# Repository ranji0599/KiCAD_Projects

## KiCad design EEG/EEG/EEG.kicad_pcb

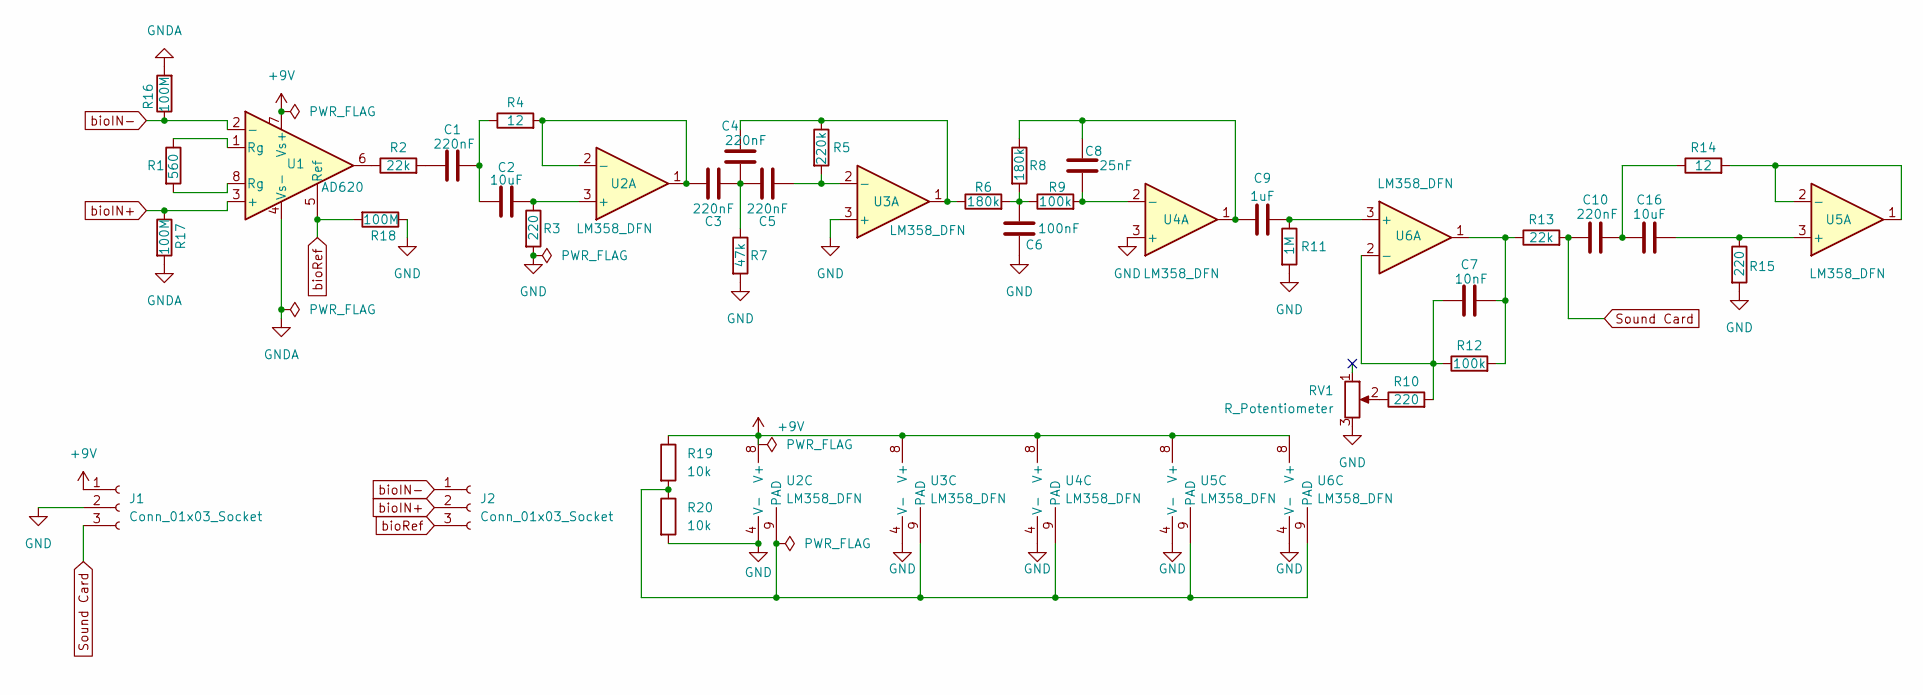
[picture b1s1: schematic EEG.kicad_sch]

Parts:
C1, C3, C4, C5, C10: 220nF; C_0805_2012Metric
C2, C16: 10uF; C_0805_2012Metric
C6: 100nF; C_0805_2012Metric
C7: 10nF; C_0805_2012Metric
C8: 25nF; C_0805_2012Metric
C9: 1uF; C_0805_2012Metric
J1, J2: Conn_01x03_Socket; JST_EH_S3B-EH_1x03_P2.50mm_Horizontal
R1: 560; R_0805_2012Metric
R2, R13: 22k; R_0805_2012Metric
R3, R10, R15: 220; R_0805_2012Metric
R4, R14: 12; R_0805_2012Metric
R5: 220k; R_0805_2012Metric
R6, R8: 180k; R_0805_2012Metric
R7: 47k; R_0805_2012Metric
R9, R12: 100k; R_0805_2012Metric
R11: 1M; R_0805_2012Metric
R16, R17, R18: 100M; R_0805_2012Metric
R19, R20: 10k; R_0805_2012Metric
RV1: R_Potentiometer; Potentiometer_ACP_CA6-H2,5_Horizontal
U1: AD620; SOIC-8_5.3x6.2mm_P1.27mm
U2, U3, U4, U5, U6: LM358_DFN; DFN-8-1EP_2x2mm_P0.5mm_EP1.05x1.75mm

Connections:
+9V: J1.1, R19.1, U1.7 (Vs+), U2.8 (V+), U3.8 (V+), U4.8 (V+), U5.8 (V+), U6.8 (V+)
unnamed: C1.1, R2.2
unnamed: C1.2, C2.1, R4.1
unnamed: C3.2, C4.2, C5.1, R7.1
unnamed: C4.1, R5.1, R6.1, U3.1
unnamed: C6.1, R6.2, R8.2, R9.1
unnamed: C7.2, R12.2, R13.1, U6.1
unnamed: C8.1, C9.1, R8.1, U4.1
unnamed: C10.2, C16.1, R14.1
unnamed: R1.1, U1.1 (Rg)
unnamed: R1.2, U1.8 (Rg)
unnamed: R2.1, U1.6
unnamed: R10.1, RV1.2
unnamed: C2.2, R3.1, U2.3 (+)
unnamed: C3.1, R4.2, U2.1, U2.2 (-)
unnamed: R19.2, R20.1, U2.9 (PAD), U3.9 (PAD), U4.9 (PAD), U5.9 (PAD), U6.9 (PAD)
unnamed: C5.2, R5.2, U3.2 (-)
unnamed: C8.2, R9.2, U4.2 (-)
unnamed: C16.2, R15.1, U5.3 (+)
unnamed: R14.2, U5.1, U5.2 (-)
unnamed: C9.2, R11.1, U6.3 (+)
unnamed: C7.1, R10.2, R12.1, U6.2 (-)
Sound Card: C10.1, J1.3, R13.2
bioIN+: J2.2, R17.1, U1.3 (+)
bioIN-: J2.1, R16.1, U1.2 (-)
bioRef: J2.3, R18.2, U1.5 (Ref)

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
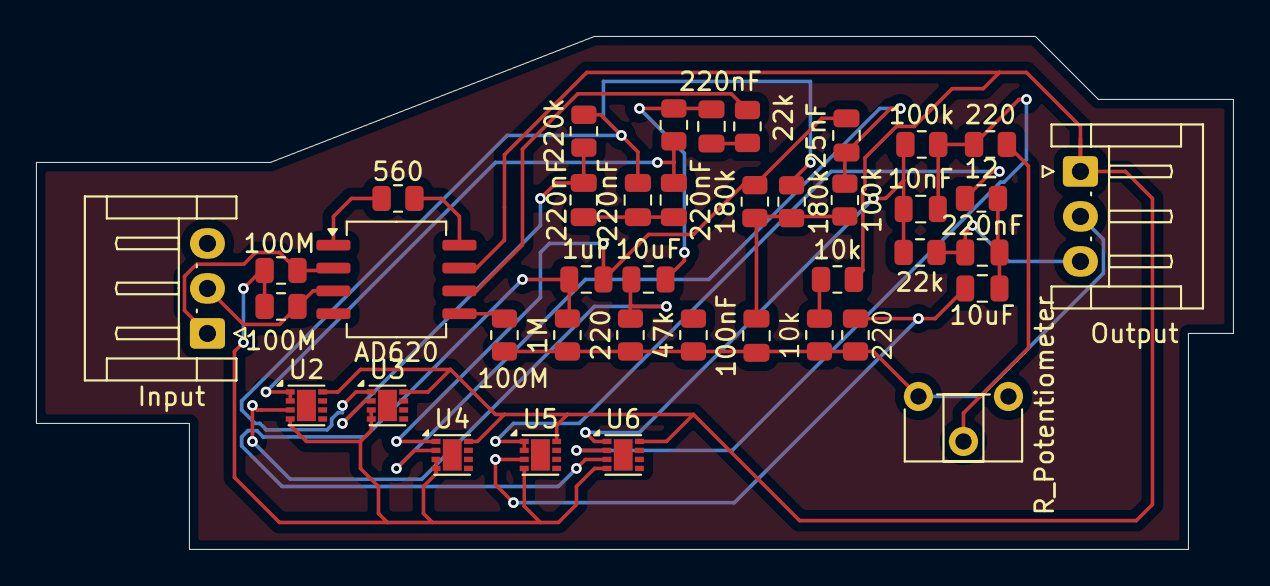
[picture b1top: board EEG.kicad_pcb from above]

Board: 2 copper layers, 66.5 x 28.5 mm, 40 parts (0 on the bottom side), 27 nets.

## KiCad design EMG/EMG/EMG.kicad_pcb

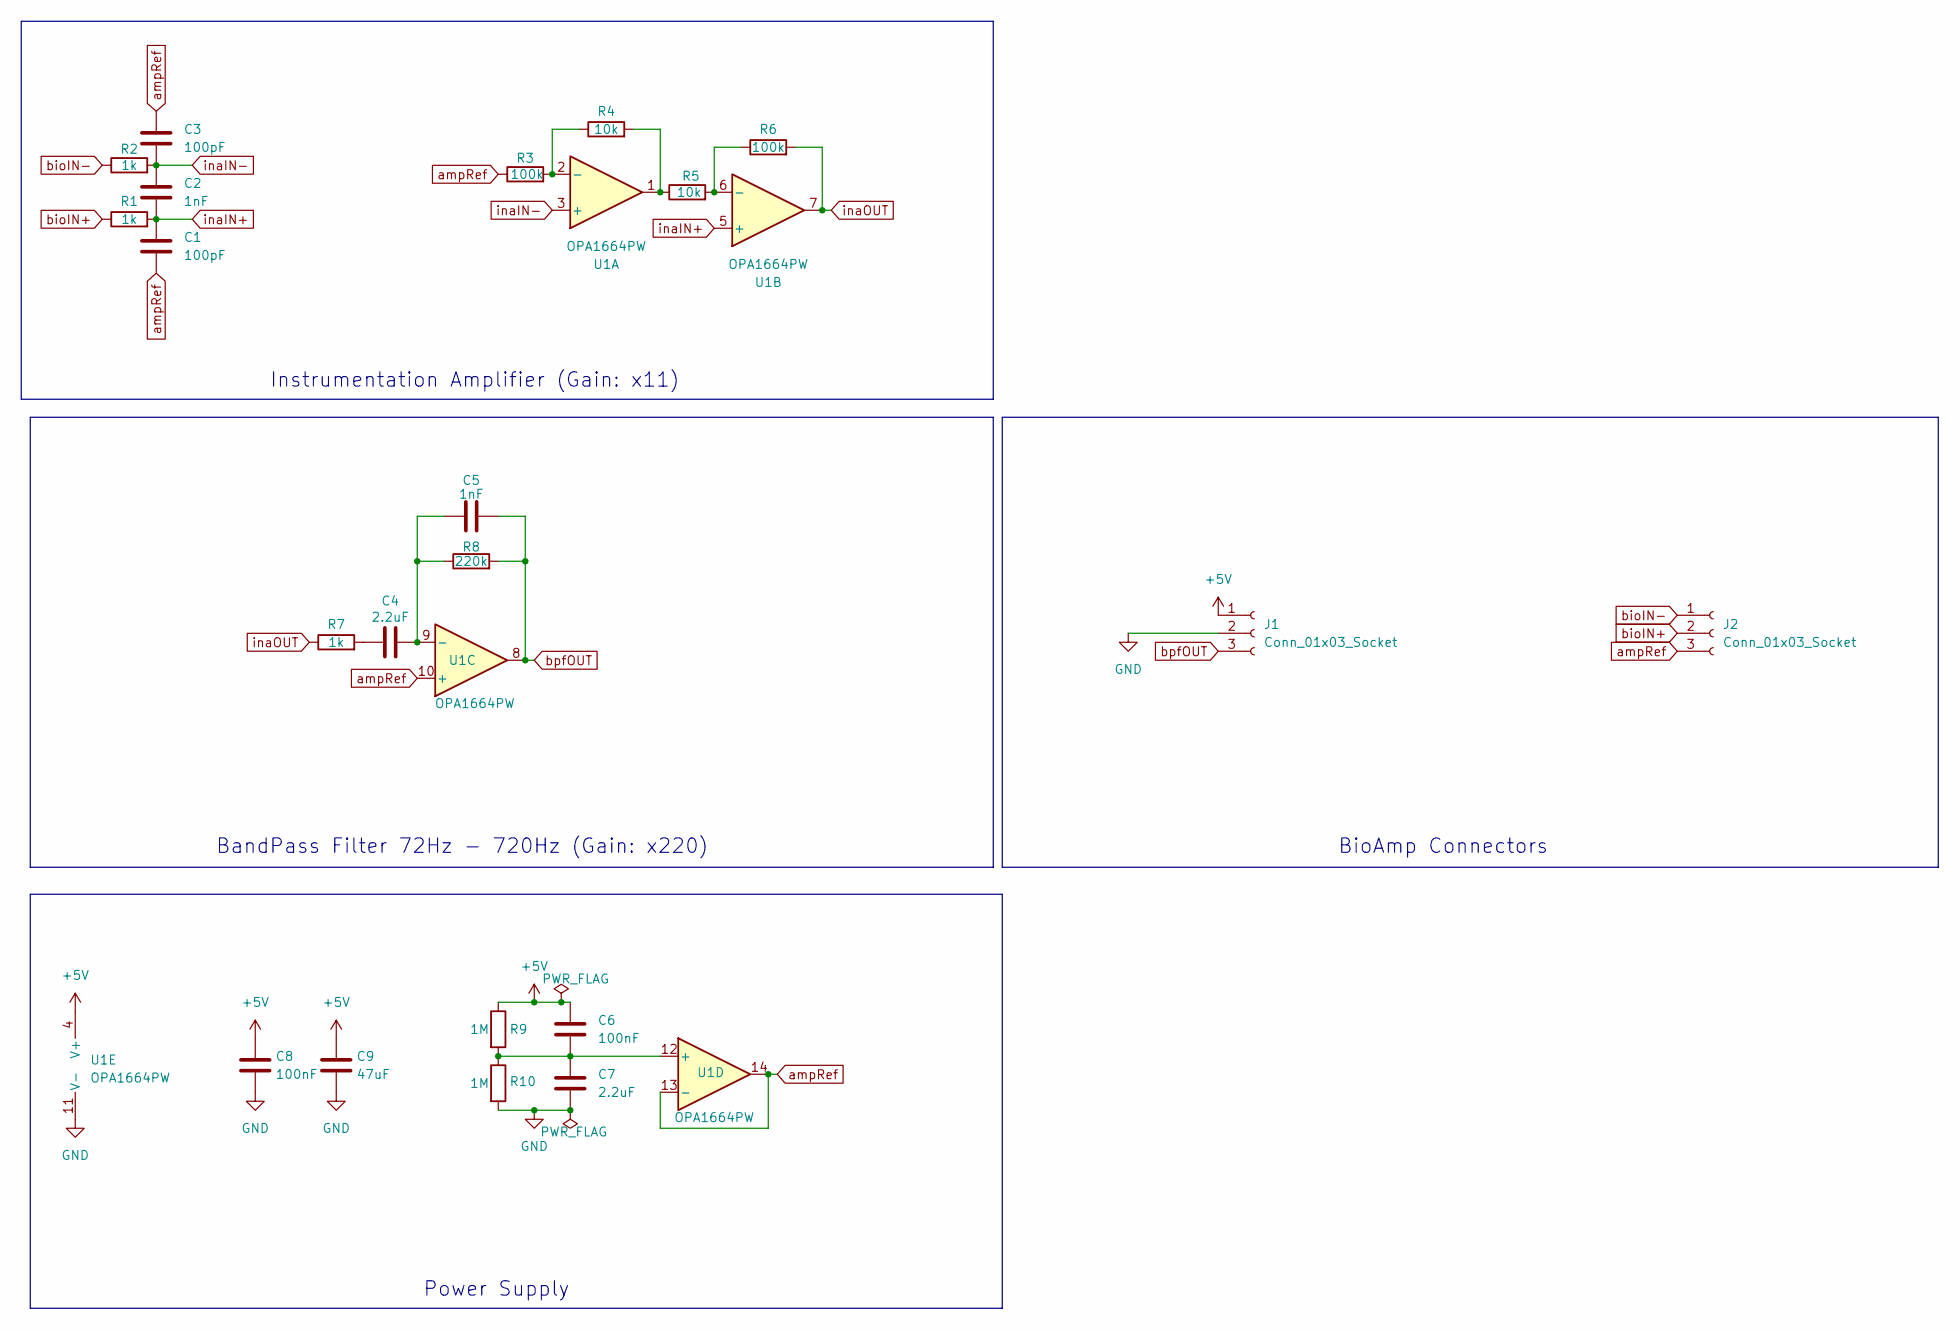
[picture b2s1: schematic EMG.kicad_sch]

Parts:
C1, C3: 100pF; C_0805_2012Metric
C2, C5: 1nF; C_0805_2012Metric
C4, C7: 2.2uF; C_0805_2012Metric
C6, C8: 100nF; C_0805_2012Metric
C9: 47uF; C_0805_2012Metric
J1, J2: Conn_01x03_Socket; JST_EH_S3B-EH_1x03_P2.50mm_Horizontal
R1, R2, R7: 1k; R_0805_2012Metric
R3, R6: 100k; R_0805_2012Metric
R4, R5: 10k; R_0805_2012Metric
R8: 220k; R_0805_2012Metric
R9, R10: 1M; R_0805_2012Metric
U1: OPA1664PW; TSSOP-14_4.4x5mm_P0.65mm

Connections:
+5V: C6.1, C8.1, C9.1, J1.1, R9.1, U1.4 (V+)
GND: C7.2, C8.2, C9.2, J1.2, R10.2, U1.11 (V-)
unnamed: C4.1, R7.2
unnamed: R4.2, R5.1, U1.1
unnamed: R3.2, R4.1, U1.2 (-)
unnamed: R5.2, R6.1, U1.6 (-)
unnamed: C4.2, C5.1, R8.1, U1.9 (-)
unnamed: C6.2, C7.1, R9.2, R10.1, U1.12 (+)
ampRef: C1.2, C3.1, J2.3, R3.1, U1.10 (+), U1.13 (-), U1.14
bioIN+: J2.2, R1.1
bioIN-: J2.1, R2.1
bpfOUT: C5.2, J1.3, R8.2, U1.8
inaIN+: C1.1, C2.2, R1.2, U1.5 (+)
inaIN-: C2.1, C3.2, R2.2, U1.3 (+)
inaOUT: R6.2, R7.1, U1.7

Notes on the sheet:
Instrumentation Amplifier (Gain: x11)
Power Supply
BandPass Filter 72Hz - 720Hz (Gain: x220)
BioAmp Connectors

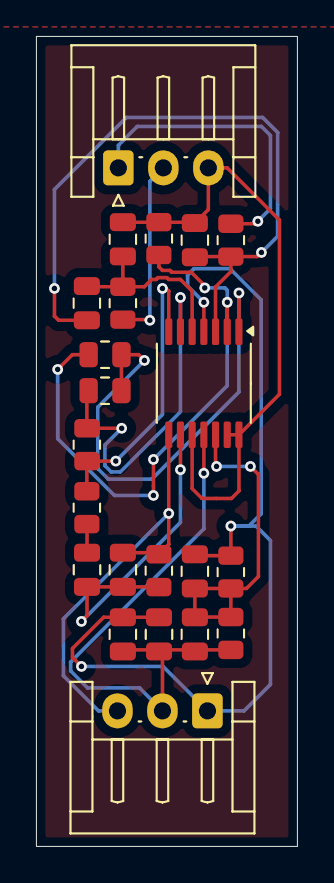
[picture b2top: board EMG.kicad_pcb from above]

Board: 2 copper layers, 14.5 x 45.0 mm, 22 parts (0 on the bottom side), 15 nets.

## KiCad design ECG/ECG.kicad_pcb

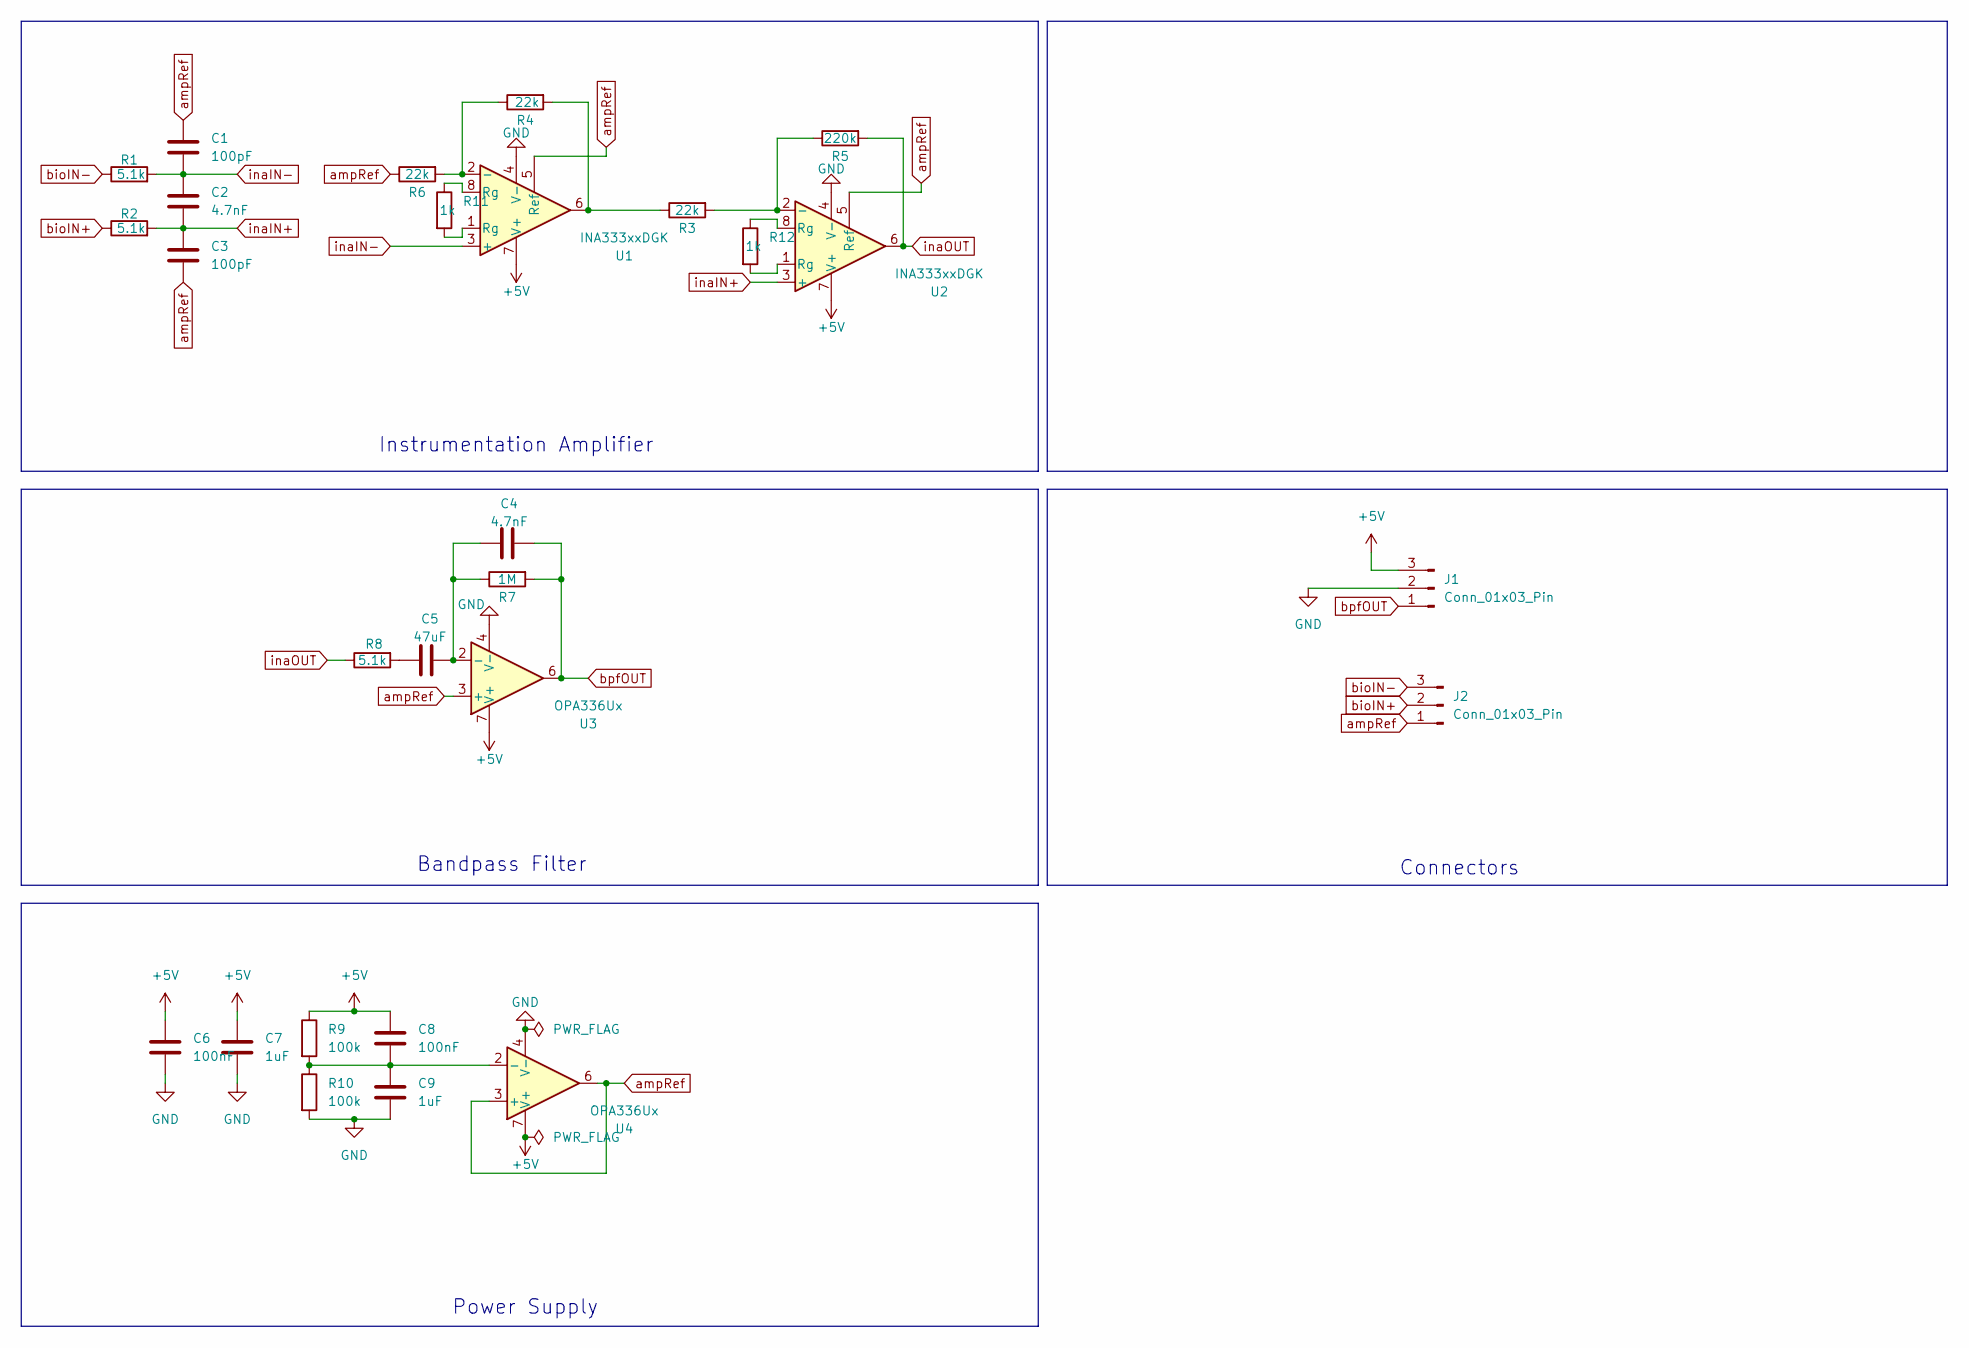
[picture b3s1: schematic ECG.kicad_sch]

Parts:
C1, C3: 100pF; C_0603_1608Metric
C2, C4: 4.7nF; C_0603_1608Metric
C5: 47uF; C_0603_1608Metric
C6, C8: 100nF; C_0603_1608Metric
C7, C9: 1uF; C_0603_1608Metric
J1: Conn_01x03_Pin; PinHeader_1x03_P1.00mm_Horizontal
J2: Conn_01x03_Pin; PinHeader_1x03_P1.27mm_Horizontal
R1, R2, R8: 5.1k; R_0805_2012Metric
R3, R4, R6: 22k; R_0603_1608Metric
R5: 220k; R_0805_2012Metric
R7: 1M; R_0805_2012Metric
R9, R10: 100k; R_0805_2012Metric
R11, R12: 1k; R_0805_2012Metric
U1, U2: INA333xxDGK; VSSOP-8_3x3mm_P0.65mm
U3, U4: OPA336Ux; SO-8_3.9x4.9mm_P1.27mm

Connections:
+5V: C6.1, C7.1, C8.1, J1.3, R9.1, U1.7 (V+), U2.7 (V+), U3.7 (V+), U4.7 (V+)
GND: C6.2, C7.2, C9.2, J1.2, R10.2, U1.4 (V-), U2.4 (V-), U3.4 (V-), U4.4 (V-)
unnamed: C5.1, R8.2
unnamed: R3.1, R4.2, U1.6
unnamed: R11.1, U1.8 (Rg)
unnamed: R11.2, U1.1 (Rg)
unnamed: R12.1, U2.8 (Rg)
unnamed: R12.2, U2.1 (Rg)
unnamed: R4.1, R6.2, U1.2 (-)
unnamed: R3.2, R5.1, U2.2 (-)
unnamed: C4.1, C5.2, R7.1, U3.2 (-)
unnamed: C8.2, C9.1, R9.2, R10.1, U4.2 (-)
ampRef: C1.1, C3.2, J2.1, R6.1, U1.5 (Ref), U2.5 (Ref), U3.3 (+), U4.3 (+), U4.6
bioIN+: J2.2, R2.1
bioIN-: J2.3, R1.1
bpfOUT: C4.2, J1.1, R7.2, U3.6
inaIN+: C2.2, C3.1, R2.2, U2.3 (+)
inaIN-: C1.2, C2.1, R1.2, U1.3 (+)
inaOUT: R5.2, R8.1, U2.6

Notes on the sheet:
Power Supply
Connectors
Instrumentation Amplifier
Bandpass Filter

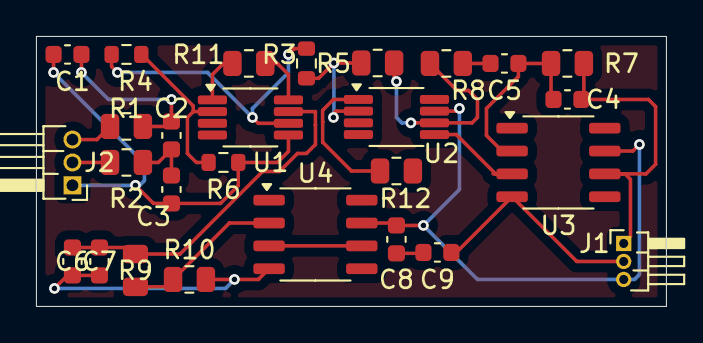
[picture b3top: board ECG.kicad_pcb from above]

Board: 2 copper layers, 35.0 x 15.0 mm, 27 parts (0 on the bottom side), 19 nets.

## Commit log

2025-07-05 Add files via upload
    This is the 1st implementation of github + KiCAD
